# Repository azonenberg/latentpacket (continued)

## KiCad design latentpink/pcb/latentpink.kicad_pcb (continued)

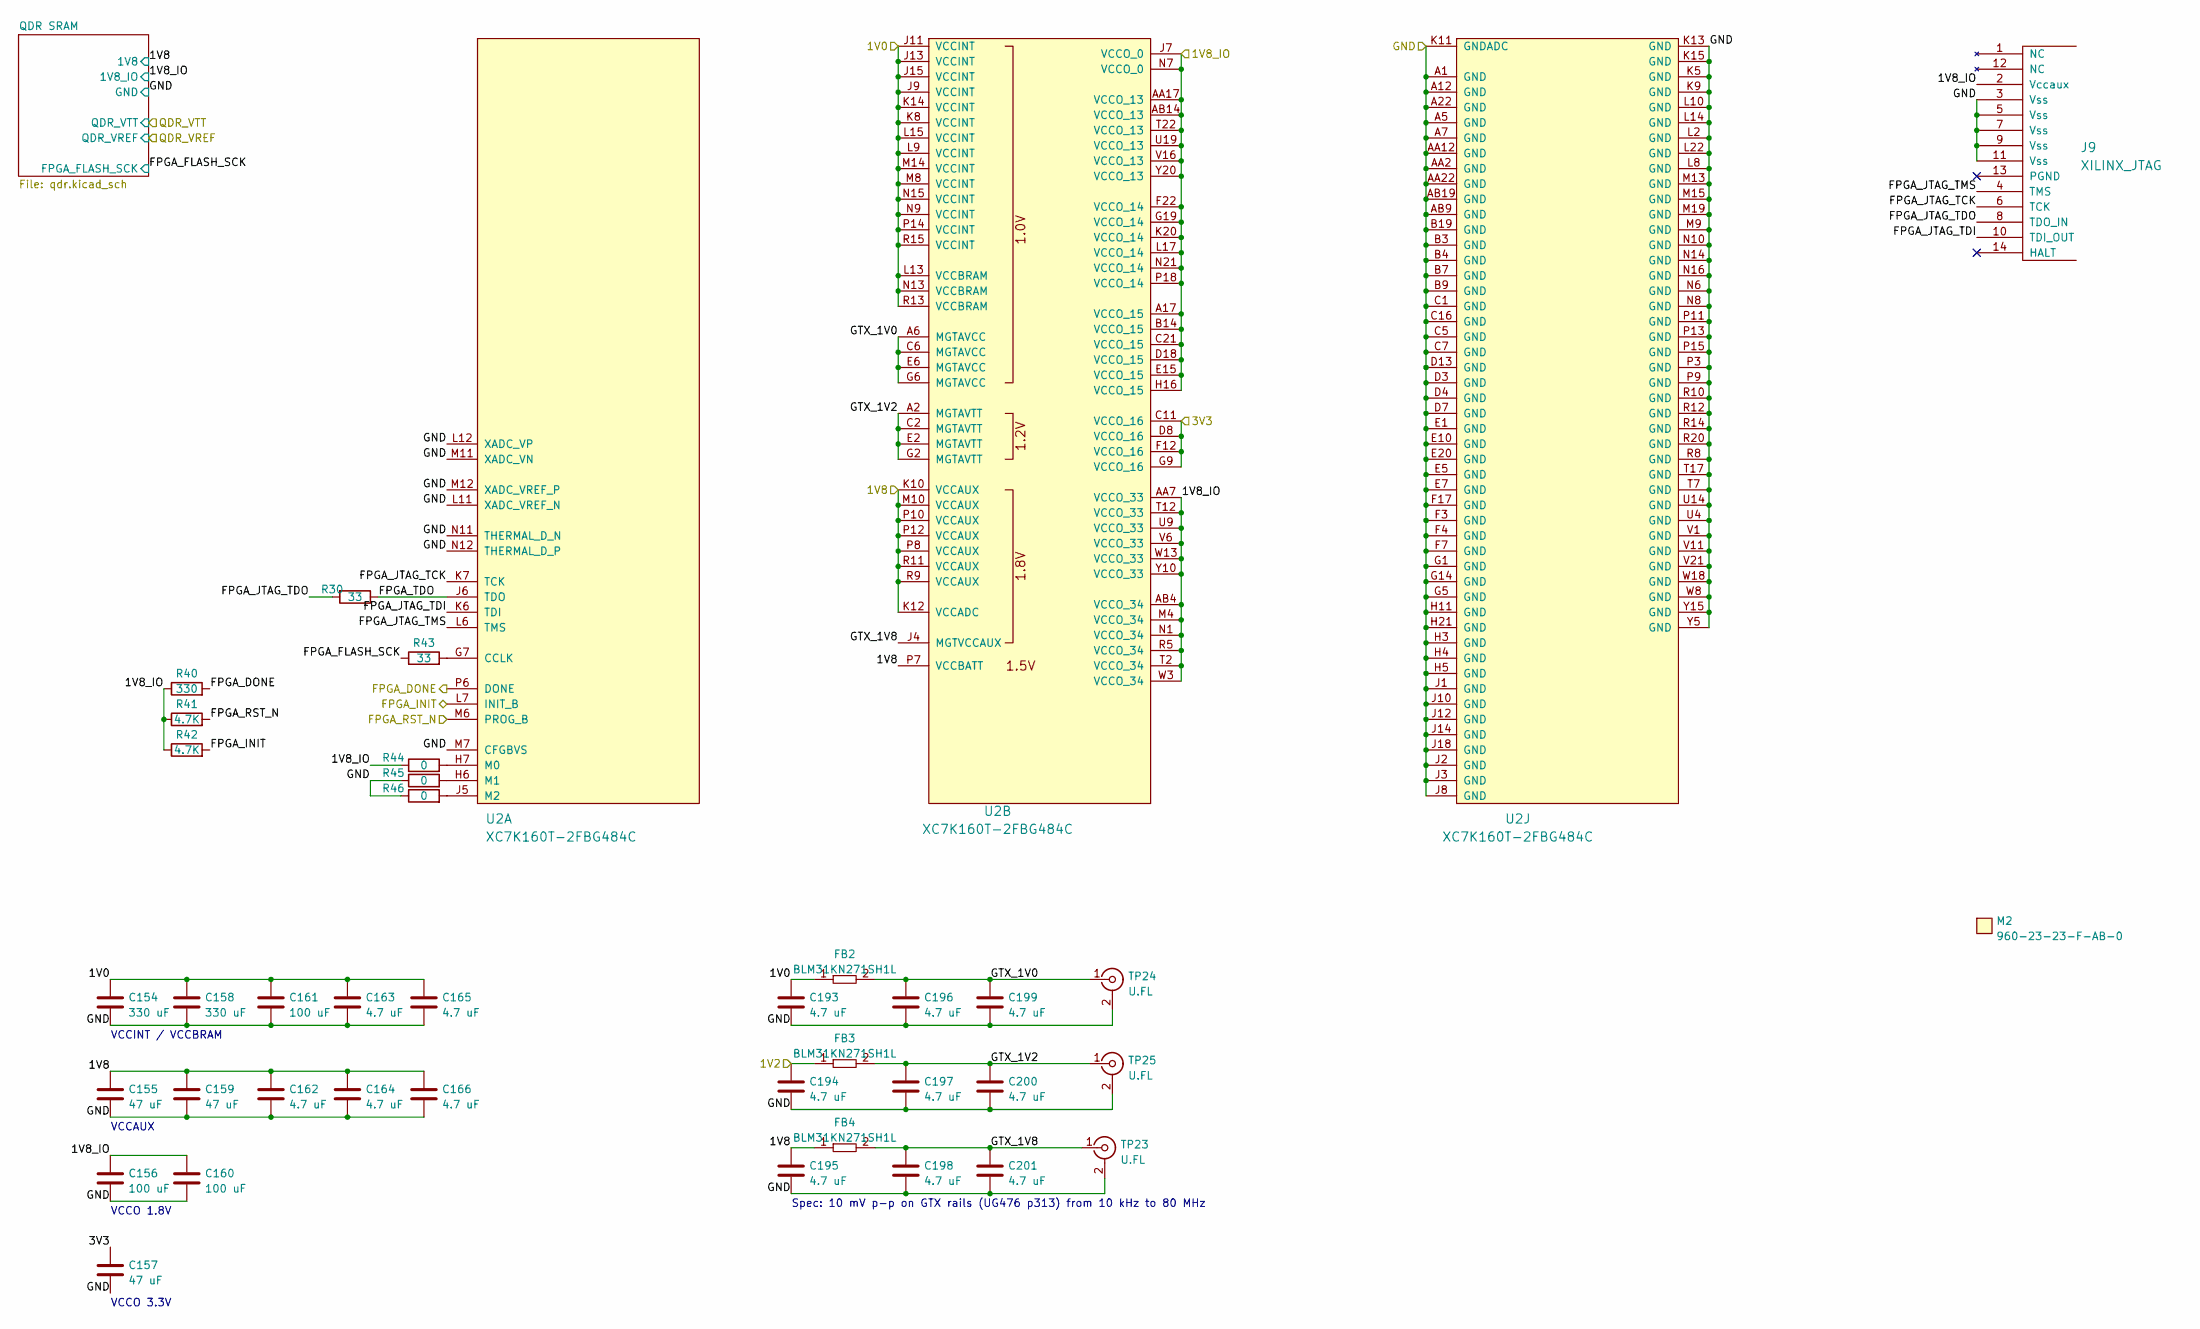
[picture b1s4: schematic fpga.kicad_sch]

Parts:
C154, C158: 330 uF; EIA_1210_CAP_NOSILK
C155, C157, C159: 47 uF; EIA_1210_CAP_NOSILK
C156, C160, C161: 100 uF; EIA_1206_CAP_NOSILK
C162, C163, C164, C165, C166, C193, C194, C195, C196, C197, C198, C199, C200, C201: 4.7 uF; EIA_0603_CAP_NOSILK
FB2, FB3, FB4: BLM31KN271SH1L; EIA_1206_CAP_NOSILK
J9: XILINX_JTAG; XILINX_JTAG_PTH_MOLEX_0878311420
M2: 960-23-23-F-AB-0; HEATSINK_WAKEFIELDVETTE_960-23-23-F-AB-0
R30, R43: 33; EIA_0402_RES_NOSILK
R40: 330; EIA_0402_RES_NOSILK
R41, R42: 4.7K; EIA_0402_RES_NOSILK
R44, R45, R46: 0; EIA_0402_RES_NOSILK
TP23, TP24, TP25: U.FL; CONN_U.FL_TE_1909763-1
U2: XC7K160T-2FBG484C; BGA_484_22x22_FULLARRAY_1MM

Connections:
/1V0: C154.1, C158.1, C161.1, C163.1, C165.1, C193.1, FB2.1, U2.J9 (VCCINT), U2.J11 (VCCINT), U2.J13 (VCCINT), U2.J15 (VCCINT), U2.K8 (VCCINT), U2.K14 (VCCINT), U2.L9 (VCCINT), U2.L13 (VCCBRAM), U2.L15 (VCCINT), U2.M8 (VCCINT), U2.M14 (VCCINT), U2.N9 (VCCINT), U2.N13 (VCCBRAM), U2.N15 (VCCINT), U2.P14 (VCCINT), U2.R13 (VCCBRAM), U2.R15 (VCCINT); also elsewhere on the board
/1V2: C194.1, FB3.1; also elsewhere on the board
/1V8: C155.1, C159.1, C162.1, C164.1, C166.1, C195.1, FB4.1, U2.K10 (VCCAUX), U2.K12 (VCCADC), U2.M10 (VCCAUX), U2.P7 (VCCBATT), U2.P8 (VCCAUX), U2.P10 (VCCAUX), U2.P12 (VCCAUX), U2.R9 (VCCAUX), U2.R11 (VCCAUX); also elsewhere on the board
/1V8_IO: C156.1, C160.1, J9.2 (Vccaux), R40.1, R41.1, R42.1, R44.1, U2.A17 (VCCO_15), U2.AA7 (VCCO_33), U2.AA17 (VCCO_13), U2.AB4 (VCCO_34), U2.AB14 (VCCO_13), U2.B14 (VCCO_15), U2.C21 (VCCO_15), U2.D18 (VCCO_15), U2.E15 (VCCO_15), U2.F22 (VCCO_14), U2.G19 (VCCO_14), U2.H16 (VCCO_15), U2.J7 (VCCO_0), U2.K20 (VCCO_14), U2.L17 (VCCO_14), U2.M4 (VCCO_34), U2.N1 (VCCO_34), U2.N7 (VCCO_0), U2.N21 (VCCO_14), U2.P18 (VCCO_14), U2.R5 (VCCO_34), U2.T2 (VCCO_34), U2.T12 (VCCO_33), U2.T22 (VCCO_13), U2.U9 (VCCO_33), U2.U19 (VCCO_13), U2.V6 (VCCO_33), U2.V16 (VCCO_13), U2.W3 (VCCO_34), U2.W13 (VCCO_33), U2.Y10 (VCCO_33), U2.Y20 (VCCO_13); also elsewhere on the board
/3V3: C157.1, U2.C11 (VCCO_16), U2.D8 (VCCO_16), U2.F12 (VCCO_16), U2.G9 (VCCO_16); also elsewhere on the board
/FPGA/FPGA_DONE: R40.2, U2.P6 (DONE); also elsewhere on the board
/FPGA/FPGA_FLASH_SCK: R43.1; also elsewhere on the board
/FPGA/FPGA_INIT: R42.2, U2.L7 (INIT_B); also elsewhere on the board
/FPGA/FPGA_JTAG_TCK: J9.6 (TCK), U2.K7 (TCK)
/FPGA/FPGA_JTAG_TDI: J9.10 (TDI_OUT), U2.K6 (TDI)
/FPGA/FPGA_JTAG_TDO: J9.8 (TDO_IN), R30.2
/FPGA/FPGA_JTAG_TMS: J9.4 (TMS), U2.L6 (TMS)
/FPGA/FPGA_RST_N: R41.2, U2.M6 (PROG_B); also elsewhere on the board
/FPGA/FPGA_TDO: R30.1, U2.J6 (TDO)
/FPGA/GTX_1V0: C196.1, C199.1, FB2.2, TP24.1 (In), U2.A6 (MGTAVCC), U2.C6 (MGTAVCC), U2.E6 (MGTAVCC), U2.G6 (MGTAVCC)
/FPGA/GTX_1V2: C197.1, C200.1, FB3.2, TP25.1 (In), U2.A2 (MGTAVTT), U2.C2 (MGTAVTT), U2.E2 (MGTAVTT), U2.G2 (MGTAVTT)
/FPGA/GTX_1V8: C198.1, C201.1, FB4.2, TP23.1 (In), U2.J4 (MGTVCCAUX)
/GND: C154.2, C155.2, C156.2, C157.2, C158.2, C159.2, C160.2, C161.2, C162.2, C163.2, C164.2, C165.2, C166.2, C193.2, C194.2, C195.2, C196.2, C197.2, C198.2, C199.2, C200.2, C201.2, J9.3 (Vss), J9.5 (Vss), J9.7 (Vss), J9.9 (Vss), J9.11 (Vss), R45.1, R46.1, TP23.2 (Ext), TP24.2 (Ext), TP25.2 (Ext), U2.A1 (GND), U2.A5 (GND), U2.A7 (GND), U2.A12 (GND), U2.A22 (GND), U2.AA2 (GND), U2.AA12 (GND), U2.AA22 (GND), U2.AB9 (GND), U2.AB19 (GND), U2.B3 (GND), U2.B4 (GND), U2.B7 (GND), U2.B9 (GND), U2.B19 (GND), U2.C1 (GND), U2.C5 (GND), U2.C7 (GND), U2.C16 (GND), U2.D3 (GND), U2.D4 (GND), U2.D7 (GND), U2.D13 (GND), U2.E1 (GND), U2.E5 (GND), U2.E7 (GND), U2.E10 (GND), U2.E20 (GND), U2.F3 (GND), U2.F4 (GND), U2.F7 (GND), U2.F17 (GND), U2.G1 (GND), U2.G5 (GND), U2.G14 (GND), U2.H3 (GND), U2.H4 (GND), U2.H5 (GND), U2.H11 (GND), U2.H21 (GND), U2.J1 (GND), U2.J2 (GND), U2.J3 (GND), U2.J8 (GND), U2.J10 (GND), U2.J12 (GND), U2.J14 (GND), U2.J18 (GND), U2.K5 (GND), U2.K9 (GND), U2.K11 (GNDADC), U2.K13 (GND), U2.K15 (GND), U2.L2 (GND), U2.L8 (GND), U2.L10 (GND), U2.L11 (XADC_VREF_N), U2.L12 (XADC_VP), U2.L14 (GND), U2.L22 (GND), U2.M7 (CFGBVS), U2.M9 (GND), U2.M11 (XADC_VN), U2.M12 (XADC_VREF_P), U2.M13 (GND), U2.M15 (GND), U2.M19 (GND), U2.N6 (GND), U2.N8 (GND), U2.N10 (GND), U2.N11 (THERMAL_D_N), U2.N12 (THERMAL_D_P), U2.N14 (GND), U2.N16 (GND), U2.P3 (GND), U2.P9 (GND), U2.P11 (GND), U2.P13 (GND), U2.P15 (GND), U2.R8 (GND), U2.R10 (GND), U2.R12 (GND), U2.R14 (GND), U2.R20 (GND), U2.T7 (GND), U2.T17 (GND), U2.U4 (GND), U2.U14 (GND), U2.V1 (GND), U2.V11 (GND), U2.V21 (GND), U2.W8 (GND), U2.W18 (GND), U2.Y5 (GND), U2.Y15 (GND); also elsewhere on the board
unnamed: R43.2, U2.G7 (CCLK)
unnamed: R44.2, U2.H7 (M0)
unnamed: R45.2, U2.H6 (M1)
unnamed: R46.2, U2.J5 (M2)

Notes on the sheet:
VCCO 1.8V
VCCO 3.3V
Spec: 10 mV p-p on GTX rails (UG476 p313) from 10 kHz to 80 MHz
VCCAUX
VCCINT / VCCBRAM

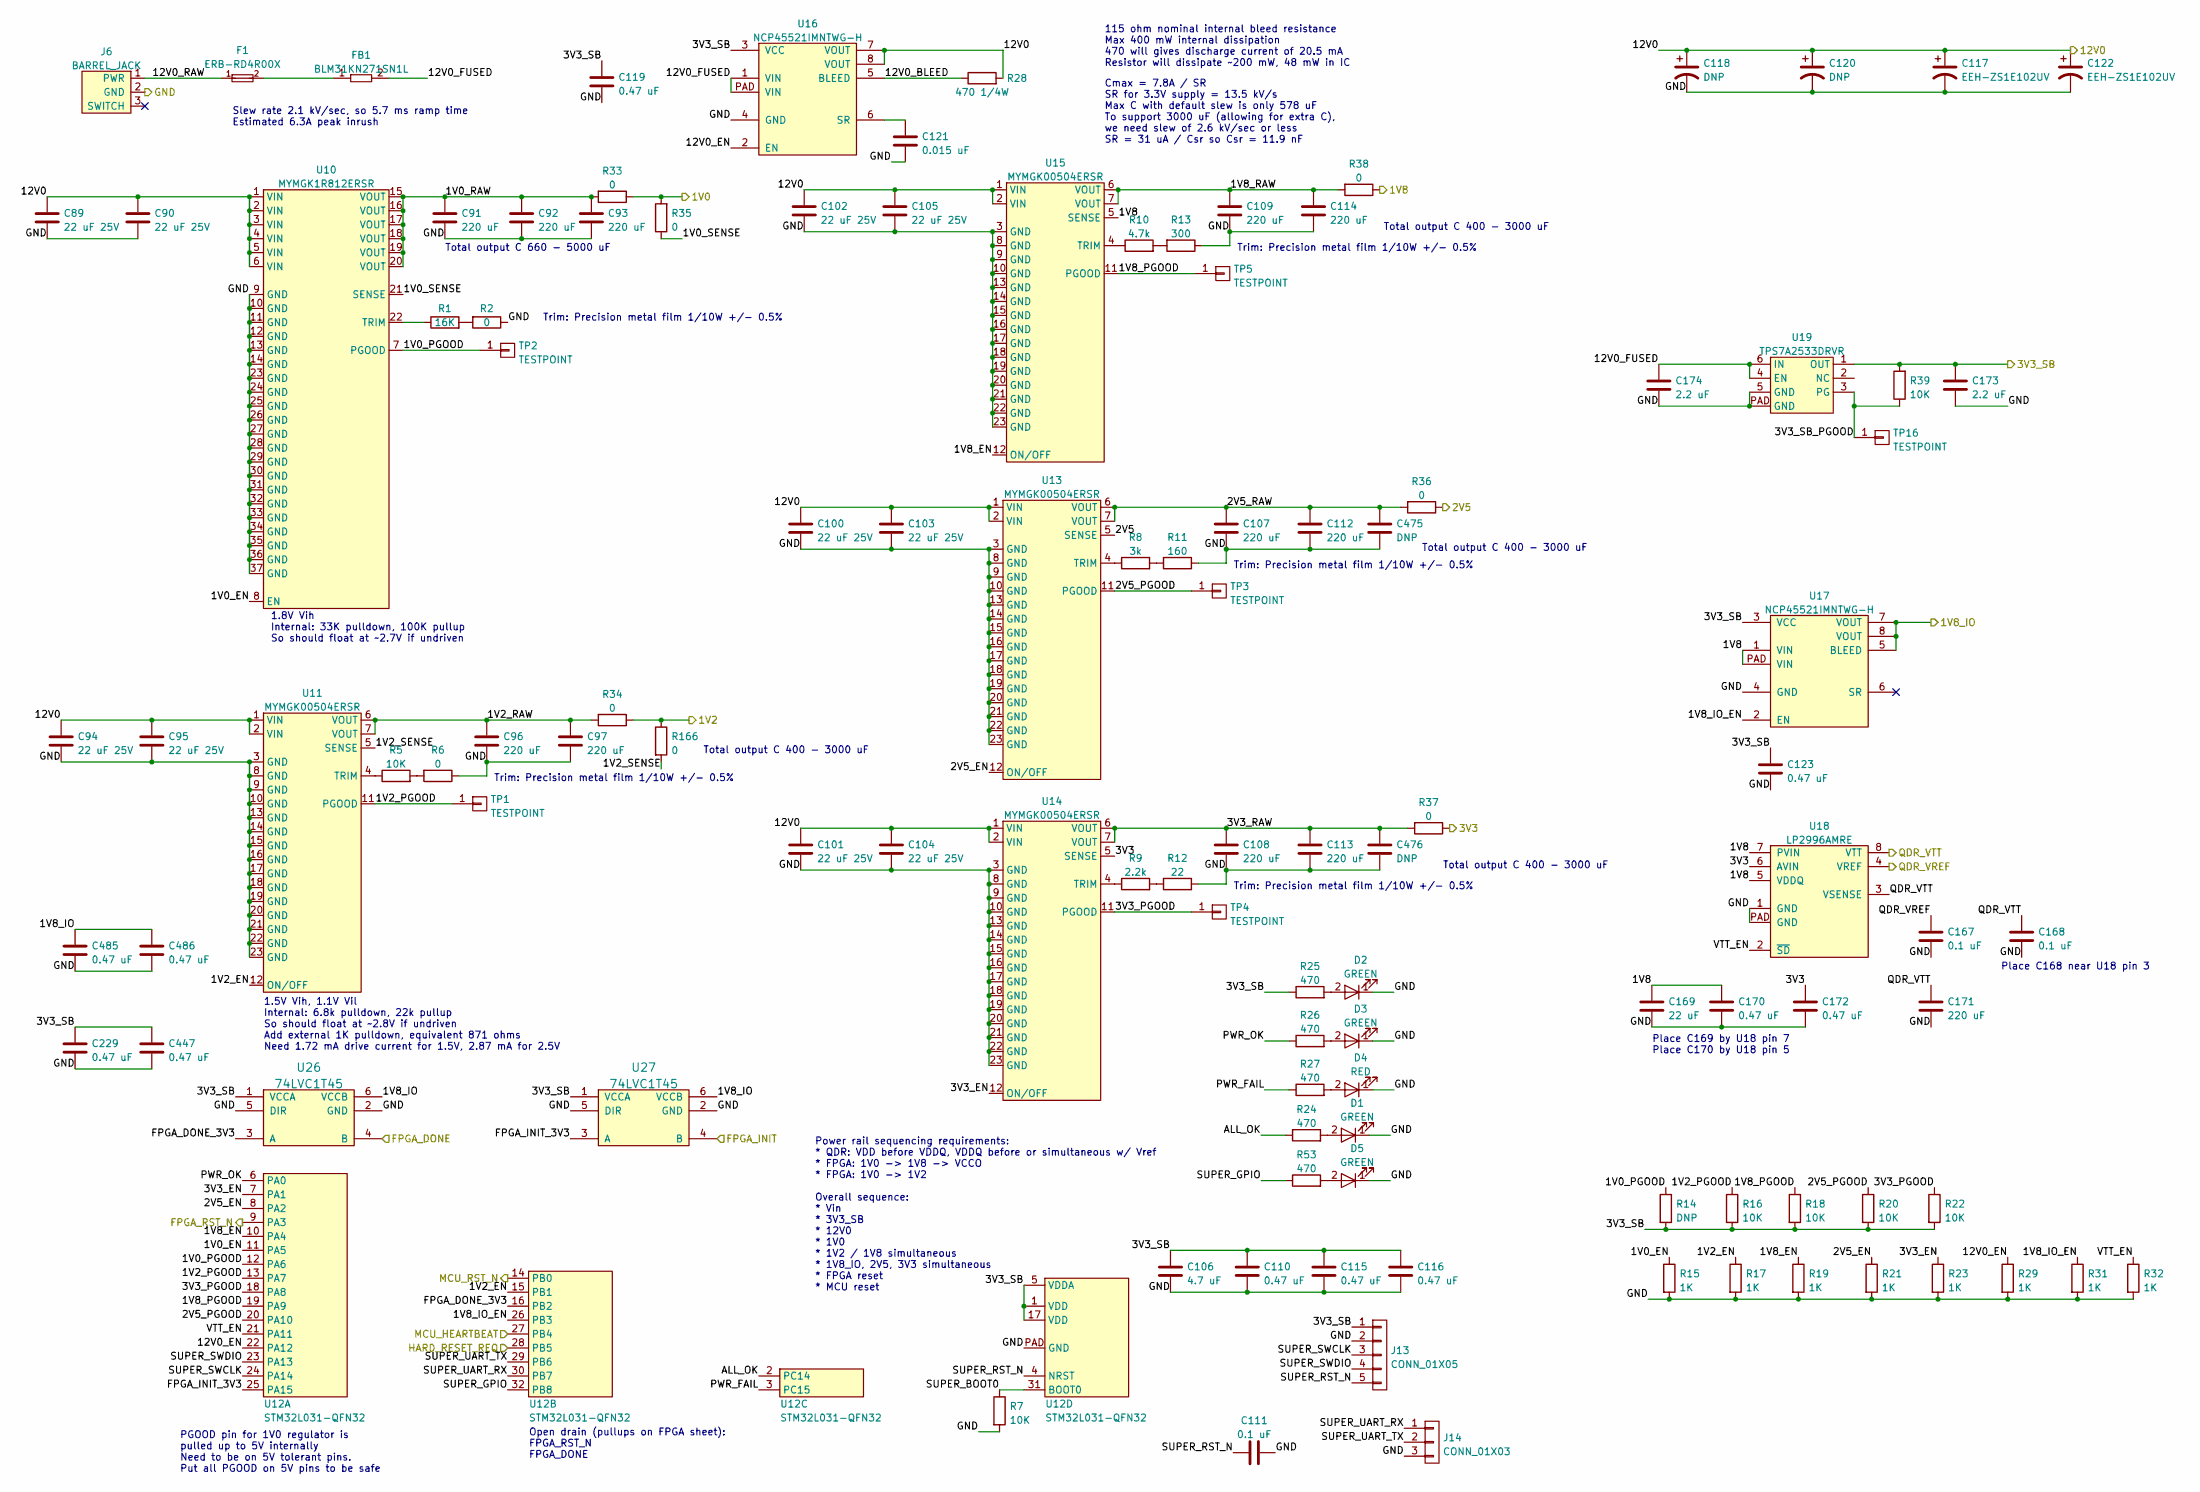
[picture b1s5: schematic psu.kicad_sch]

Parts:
C89, C90, C94, C95, C100, C101, C102, C103, C104, C105: 22 uF 25V; EIA_1812_CAP_NOSILK
C91, C92, C93, C96, C97, C107, C108, C109, C112, C113, C114, C171: 220 uF; EIA_1210_CAP_NOSILK
C106: 4.7 uF; EIA_0603_CAP_NOSILK
C110, C115, C116, C119, C123, C170, C172, C229, C447, C485, C486: 0.47 uF; EIA_0402_CAP_NOSILK
C111, C167, C168: 0.1 uF; EIA_0402_CAP_NOSILK
C117, C122: EEH-ZS1E102UV; CAP_AL_10MM_SMT
C118, C120: DNP; CAP_AL_10MM_SMT
C121: 0.015 uF; EIA_0603_CAP_NOSILK
C169: 22 uF; EIA_1206_CAP_NOSILK
C173, C174: 2.2 uF; EIA_0805_CAP_NOSILK
C475, C476: DNP; EIA_1210_CAP_NOSILK
D1, D2, D3, D5: GREEN; EIA_0603_LED
D4: RED; EIA_0603_LED
F1: ERB-RD4R00X; EIA_0402_CAP_NOSILK
FB1: BLM31KN271SN1L; EIA_1206_CAP_NOSILK
J6: BARREL_JACK; CONN_CUI_PJ-058BH_HIPWR_BARREL_NOSLOT
J13: CONN_01X05; CONN_HEADER_2.54MM_1x5
J14: CONN_01X03; CONN_HEADER_2.54MM_1x3
R1: 16K; EIA_0402_RES_NOSILK
R2, R6, R33, R34, R35, R36, R37, R38, R166: 0; EIA_0402_RES_NOSILK
R5, R7, R16, R18, R20, R22, R39: 10K; EIA_0402_RES_NOSILK
R8: 3k; EIA_0402_RES_NOSILK
R9: 2.2k; EIA_0402_RES_NOSILK
R10: 4.7k; EIA_0402_RES_NOSILK
R11: 160; EIA_0402_RES_NOSILK
R12: 22; EIA_0402_RES_NOSILK
R13: 300; EIA_0402_RES_NOSILK
R14: DNP; EIA_0402_RES_NOSILK
R15, R17, R19, R21, R23, R29, R31, R32: 1K; EIA_0402_RES_NOSILK
R24, R25, R26, R27, R53: 470; EIA_0402_RES_NOSILK
R28: 470 1/4W; EIA_0603_RES_NOSILK
TP1, TP2, TP3, TP4, TP5, TP16: TESTPOINT; TESTPOINT_SMT_0.5MM
U10: MYMGK1R812ERSR; MODULE_MURATA_MYMGK1R812
U11, U13, U14, U15: MYMGK00504ERSR; MODULE_MURATA_MYMGK00504ERSR
U12: STM32L031-QFN32; QFN_32_0.5MM_5x5MM
U16, U17: NCP45521IMNTWG-H; DFN_8_0.5MM_2x2MM
U18: LP2996AMRE; SOIC_8_3.9MM_EPAD
U19: TPS7A2533DRVR; DFN_6_0.65MM_2x2MM
U26, U27: 74LVC1T45; DFN_6_0.5MM_1.45x1.00MM

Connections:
/1V0: R33.1, R35.2; also elsewhere on the board
/1V2: R34.1, R166.1; also elsewhere on the board
/1V8: C169.1, C170.1, R38.1, U15.5 (SENSE), U17.1 (VIN), U17.PAD (VIN), U18.5 (VDDQ), U18.7 (PVIN); also elsewhere on the board
/1V8_IO: C485.1, C486.1, U17.5 (BLEED), U17.7 (VOUT), U17.8 (VOUT), U26.6 (VCCB), U27.6 (VCCB); also elsewhere on the board
/2V5: R36.1, U13.5 (SENSE); also elsewhere on the board
/3V3: C172.1, R37.1, U14.5 (SENSE), U18.6 (AVIN); also elsewhere on the board
/3V3_SB: C106.1, C110.1, C115.1, C116.1, C119.1, C123.1, C173.1, C229.1, C447.1, J13.1, R14.2, R16.2, R18.2, R20.2, R22.2, R25.1, R39.2, U12.1 (VDD), U12.5 (VDDA), U12.17 (VDD), U16.3 (VCC), U17.3 (VCC), U19.1 (OUT), U26.1 (VCCA), U27.1 (VCCA); also elsewhere on the board
/12V0: C89.1, C90.1, C94.1, C95.1, C100.1, C101.1, C102.1, C103.1, C104.1, C105.1, C117.1, C118.1, C120.1, C122.1, R28.2, U10.1 (VIN), U10.2 (VIN), U10.3 (VIN), U10.4 (VIN), U10.5 (VIN), U10.6 (VIN), U11.1 (VIN), U11.2 (VIN), U13.1 (VIN), U13.2 (VIN), U14.1 (VIN), U14.2 (VIN), U15.1 (VIN), U15.2 (VIN), U16.7 (VOUT), U16.8 (VOUT); also elsewhere on the board
/FPGA/FPGA_DONE: U26.4 (B); also elsewhere on the board
/FPGA/FPGA_INIT: U27.4 (B); also elsewhere on the board
/FPGA/FPGA_RST_N: U12.9 (PA3); also elsewhere on the board
/GND: C89.2, C90.2, C91.2, C92.2, C93.2, C94.2, C95.2, C96.2, C97.2, C100.2, C101.2, C102.2, C103.2, C104.2, C105.2, C106.2, C107.2, C108.2, C109.2, C110.2, C111.2, C112.2, C113.2, C114.2, C115.2, C116.2, C117.2, C118.2, C119.2, C120.2, C121.2, C122.2, C123.2, C167.2, C168.2, C169.2, C170.2, C171.2, C172.2, C173.2, C174.2, C229.2, C447.2, C475.2, C476.2, C485.2, C486.2, D1.1 (K), D2.1 (K), D3.1 (K), D4.1 (K), D5.1 (K), J6.2 (GND), J13.2, J14.3, R2.1, R6.1, R7.2, R11.1, R12.1, R13.1, R15.2, R17.2, R19.2, R21.2, R23.2, R29.2, R31.2, R32.2, U10.9 (GND), U10.10 (GND), U10.11 (GND), U10.12 (GND), U10.13 (GND), U10.14 (GND), U10.23 (GND), U10.24 (GND), U10.25 (GND), U10.26 (GND), U10.27 (GND), U10.28 (GND), U10.29 (GND), U10.30 (GND), U10.31 (GND), U10.32 (GND), U10.33 (GND), U10.34 (GND), U10.35 (GND), U10.36 (GND), U10.37 (GND), U11.3 (GND), U11.8 (GND), U11.9 (GND), U11.10 (GND), U11.13 (GND), U11.14 (GND), U11.15 (GND), U11.16 (GND), U11.17 (GND), U11.18 (GND), U11.19 (GND), U11.20 (GND), U11.21 (GND), U11.22 (GND), U11.23 (GND), U12.PAD (GND), U13.3 (GND), U13.8 (GND), U13.9 (GND), U13.10 (GND), U13.13 (GND), U13.14 (GND), U13.15 (GND), U13.16 (GND), U13.17 (GND), U13.18 (GND), U13.19 (GND), U13.20 (GND), U13.21 (GND), U13.22 (GND), U13.23 (GND), U14.3 (GND), U14.8 (GND), U14.9 (GND), U14.10 (GND), U14.13 (GND), U14.14 (GND), U14.15 (GND), U14.16 (GND), U14.17 (GND), U14.18 (GND), U14.19 (GND), U14.20 (GND), U14.21 (GND), U14.22 (GND), U14.23 (GND), U15.3 (GND), U15.8 (GND), U15.9 (GND), U15.10 (GND), U15.13 (GND), U15.14 (GND), U15.15 (GND), U15.16 (GND), U15.17 (GND), U15.18 (GND), U15.19 (GND), U15.20 (GND), U15.21 (GND), U15.22 (GND), U15.23 (GND), U16.4 (GND), U17.4 (GND), U18.1 (GND), U18.PAD (GND), U19.5 (GND), U19.PAD (GND), U26.2 (GND), U26.5 (DIR), U27.2 (GND), U27.5 (DIR); also elsewhere on the board
/MCU_RST_N: U12.14 (PB0); also elsewhere on the board
/Management/HARD_RESET_REQ: U12.28 (PB5); also elsewhere on the board
/Management/MCU_HEARTBEAT: U12.27 (PB4); also elsewhere on the board
/Power Supply/1V0_EN: R15.1, U10.8 (EN), U12.11 (PA5)
/Power Supply/1V0_PGOOD: R14.1, TP2.1, U10.7 (PGOOD), U12.12 (PA6)
/Power Supply/1V0_RAW: C91.1, C92.1, C93.1, R33.2, U10.15 (VOUT), U10.16 (VOUT), U10.17 (VOUT), U10.18 (VOUT), U10.19 (VOUT), U10.20 (VOUT)
/Power Supply/1V0_SENSE: R35.1, U10.21 (SENSE)
/Power Supply/1V2_EN: R17.1, U11.12 (ON/OFF), U12.15 (PB1)
/Power Supply/1V2_PGOOD: R16.1, TP1.1, U11.11 (PGOOD), U12.13 (PA7)
/Power Supply/1V2_RAW: C96.1, C97.1, R34.2, U11.6 (VOUT), U11.7 (VOUT)
/Power Supply/1V2_SENSE: R166.2, U11.5 (SENSE)
/Power Supply/1V8_EN: R19.1, U12.10 (PA4), U15.12 (ON/OFF)
/Power Supply/1V8_IO_EN: R31.1, U12.26 (PB3), U17.2 (EN)
/Power Supply/1V8_PGOOD: R18.1, TP5.1, U12.19 (PA9), U15.11 (PGOOD)
/Power Supply/1V8_RAW: C109.1, C114.1, R38.2, U15.6 (VOUT), U15.7 (VOUT)
/Power Supply/2V5_EN: R21.1, U12.8 (PA2), U13.12 (ON/OFF)
/Power Supply/2V5_PGOOD: R20.1, TP3.1, U12.20 (PA10), U13.11 (PGOOD)
/Power Supply/2V5_RAW: C107.1, C112.1, C475.1, R36.2, U13.6 (VOUT), U13.7 (VOUT)
/Power Supply/3V3_EN: R23.1, U12.7 (PA1), U14.12 (ON/OFF)
/Power Supply/3V3_PGOOD: R22.1, TP4.1, U12.18 (PA8), U14.11 (PGOOD)
/Power Supply/3V3_RAW: C108.1, C113.1, C476.1, R37.2, U14.6 (VOUT), U14.7 (VOUT)
/Power Supply/3V3_SB_PGOOD: R39.1, TP16.1, U19.3 (PG)
/Power Supply/12V0_BLEED: R28.1, U16.5 (BLEED)
/Power Supply/12V0_EN: R29.1, U12.22 (PA12), U16.2 (EN)
/Power Supply/12V0_FUSED: C174.1, FB1.2, U16.1 (VIN), U16.PAD (VIN), U19.4 (EN), U19.6 (IN)
/Power Supply/12V0_RAW: F1.1, J6.1 (PWR)
/Power Supply/ALL_OK: R24.1, U12.2 (PC14)
/Power Supply/FPGA_DONE_3V3: U12.16 (PB2), U26.3 (A)
/Power Supply/FPGA_INIT_3V3: U12.25 (PA15), U27.3 (A)
/Power Supply/PWR_FAIL: R27.1, U12.3 (PC15)
/Power Supply/PWR_OK: R26.1, U12.6 (PA0)
/Power Supply/SUPER_BOOT0: R7.1, U12.31 (BOOT0)
/Power Supply/SUPER_GPIO: R53.1, U12.32 (PB8)
/Power Supply/SUPER_RST_N: C111.1, J13.5, U12.4 (NRST)
/Power Supply/SUPER_SWCLK: J13.3, U12.24 (PA14)
/Power Supply/SUPER_SWDIO: J13.4, U12.23 (PA13)
/Power Supply/SUPER_UART_RX: J14.1, U12.30 (PB7)
/Power Supply/SUPER_UART_TX: J14.2, U12.29 (PB6)
/Power Supply/VTT_EN: R32.1, U12.21 (PA11), U18.2 (~SD)
/QDR_VREF: C167.1, U18.4 (VREF); also elsewhere on the board
/QDR_VTT: C168.1, C171.1, U18.3 (VSENSE), U18.8 (VTT); also elsewhere on the board
unnamed: C121.1, U16.6 (SR)
unnamed: D1.2 (A), R24.2
unnamed: D2.2 (A), R25.2
unnamed: D3.2 (A), R26.2
unnamed: D4.2 (A), R27.2
unnamed: D5.2 (A), R53.2
unnamed: F1.2, FB1.1
unnamed: R1.1, U10.22 (TRIM)
unnamed: R1.2, R2.2
unnamed: R5.1, U11.4 (TRIM)
unnamed: R5.2, R6.2
unnamed: R8.1, U13.4 (TRIM)
unnamed: R9.1, U14.4 (TRIM)
unnamed: R10.1, U15.4 (TRIM)
unnamed: R10.2, R13.2
unnamed: R8.2, R11.2
unnamed: R9.2, R12.2

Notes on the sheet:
Total output C 400 - 3000 uF
Place C168 near U18 pin 3
Power rail sequencing requirements: * QDR: VDD before VDDQ, VDDQ before or simultaneous w/ Vref * FPGA: 1V0 -> 1V8 -> VCCO * FPGA: 1V0 -> 1V2 Overall sequence: * Vin * 3V3_SB * 12V0 * 1V0 * 1V2 / 1V8 simultaneous * 1V8_IO, 2V5, 3V3 simultaneous * FPGA reset * MCU reset
Cmax = 7.8A / SR SR for 3.3V supply = 13.5 kV/s Max C with default slew is only 578 uF To support 3000 uF (allowing for extra C), we need slew of 2.6 kV/sec or less SR = 31 uA / Csr so Csr = 11.9 nF
Trim: Precision metal film 1/10W +/- 0.5%
Total output C 660 - 5000 uF
115 ohm nominal internal bleed resistance Max 400 mW internal dissipation 470 will gives discharge current of 20.5 mA Resistor will dissipate ~200 mW, 48 mW in IC
1.5V Vih, 1.1V Vil Internal: 6.8k pulldown, 22k pullup So should float at ~2.8V if undriven Add external 1K pulldown, equivalent 871 ohms Need 1.72 mA drive current for 1.5V, 2.87 mA for 2.5V
Open drain (pullups on FPGA sheet): FPGA_RST_N FPGA_DONE
1.8V Vih Internal: 33K pulldown, 100K pullup So should float at ~2.7V if undriven
PGOOD pin for 1V0 regulator is pulled up to 5V internally Need to be on 5V tolerant pins. Put all PGOOD on 5V pins to be safe
Place C169 by U18 pin 7 Place C170 by U18 pin 5
Slew rate 2.1 kV/sec, so 5.7 ms ramp time Estimated 6.3A peak inrush
